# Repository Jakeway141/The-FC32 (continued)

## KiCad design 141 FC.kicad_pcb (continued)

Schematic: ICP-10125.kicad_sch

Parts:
C41, C43, C44, C75: 100nF; C_0603_1608Metric
C55: 1uF; C_0603_1608Metric
FB4: 1K/0.1A; L_0603_1608Metric
IC2: ICP-10125; ICP10125; Manufacturer_Part_Number ICP-10125; Mouser Part Number 410-ICP-10125
R17, R18: 3.3K; R_0603_1608Metric
R19, R20: 10K; R_0603_1608Metric
U2: SHT4x; Sensirion_DFN-4_1.5x1.5mm_P0.8mm_SHT4x_NoCentralPad
U6: TCA9517ADGK; VSSOP-8_3x3mm_P0.65mm

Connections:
/Barometer/SCL: R20.2, U2.2 (SCL), U6.7 (SCLB); also elsewhere on the board
/Barometer/SDA: R19.2, U2.1 (SDA), U6.6 (SDAB); also elsewhere on the board
/Barometer/SDA_BAR: IC2.4 (SDA), R18.2, U6.3 (SDAA)
unnamed: IC2.2 (SCL), R17.2, U6.2 (SCLA)
VDD: C44.1, R19.1, R20.1, U6.8 (VCCB); also elsewhere on the board
VDDBAR: C41.2, C43.2, C55.2, FB4.1, IC2.5 (VDD), R17.1, R18.1, U6.1 (VCCA)
VDDIMU_1_IO: C75.2, U2.3 (VDD); also elsewhere on the board
VDD_1V8: FB4.2; also elsewhere on the board

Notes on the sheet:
Level Shifting
Temperature Sensor

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
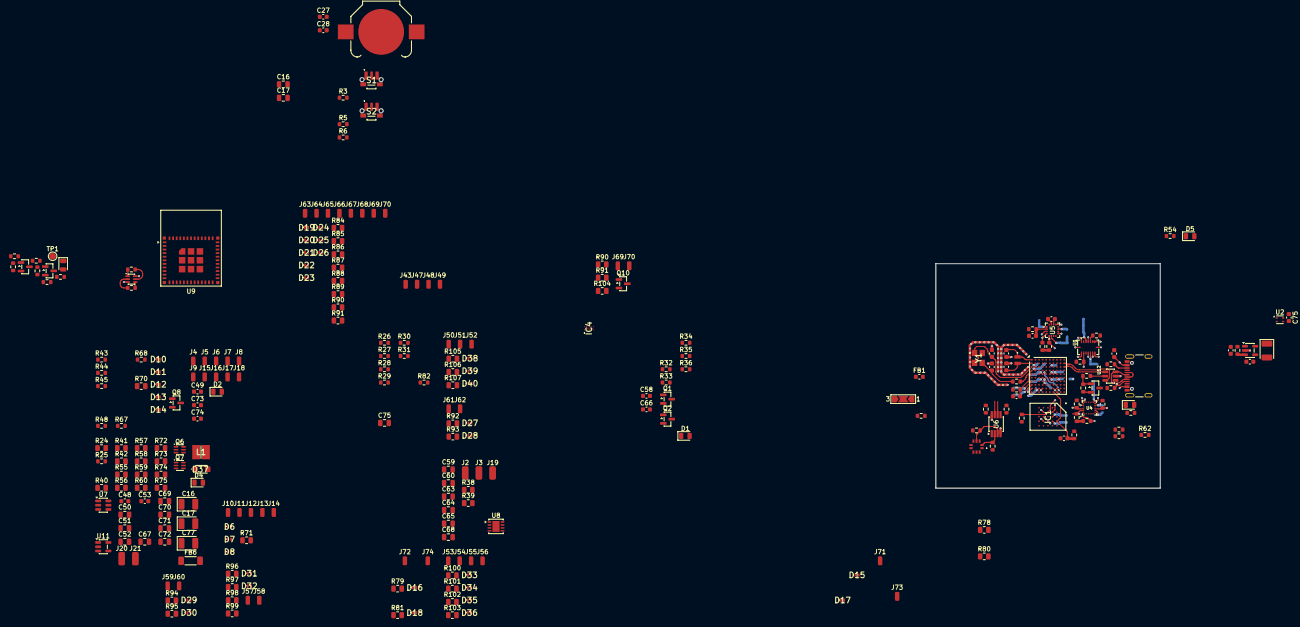
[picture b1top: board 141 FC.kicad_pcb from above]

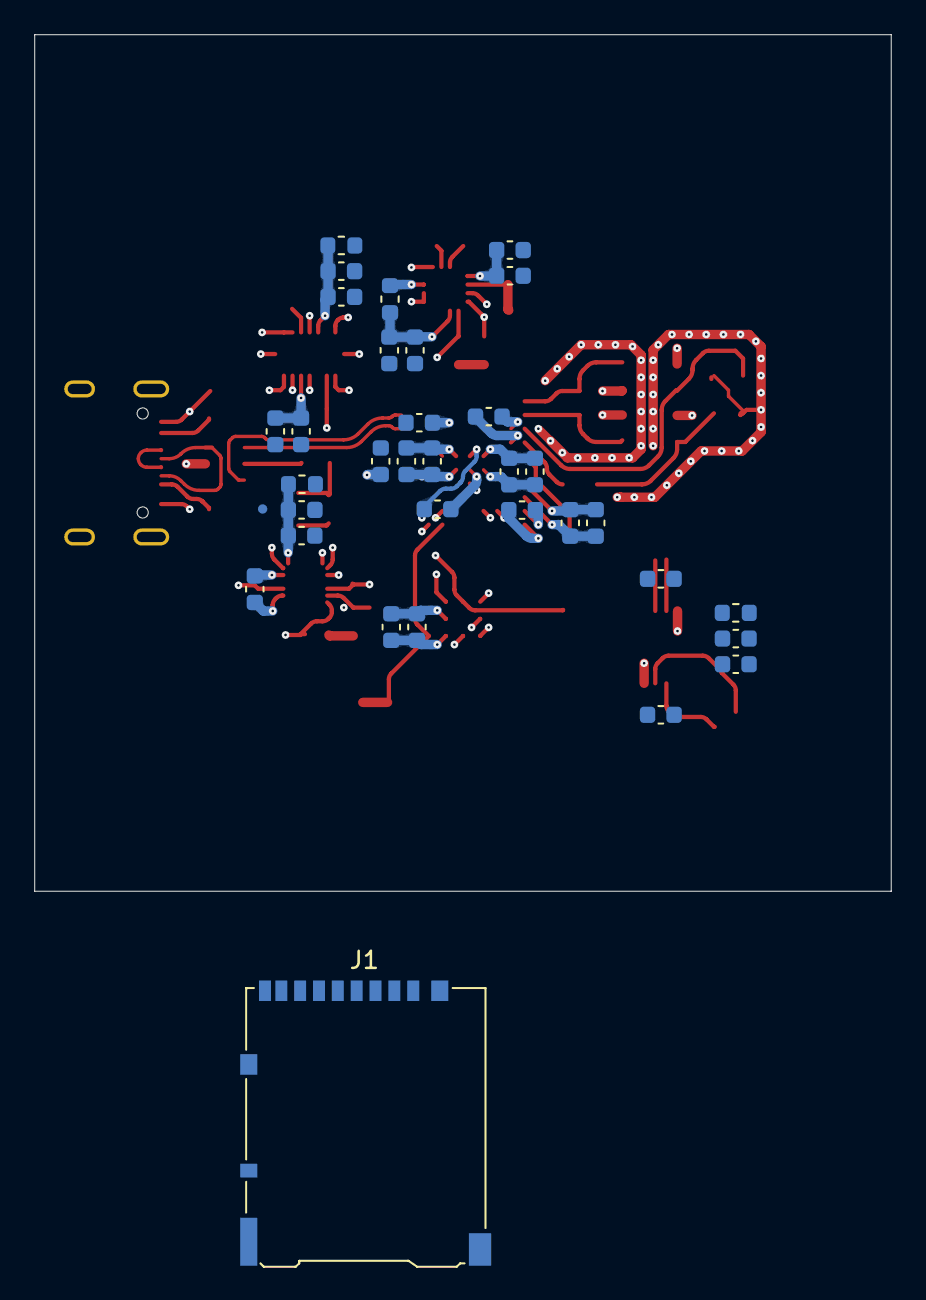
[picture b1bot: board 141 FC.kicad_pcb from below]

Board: 6 copper layers, 50.0 x 50.0 mm, 309 parts (33 on the bottom side), 190 nets.

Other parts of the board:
C16#2, C17#2, C75#2: 100nF; C_0805_2012Metric
D19, D20: PESD3V3X1BL,315; PESD5V0S1BL315
J43: M; SolderWirePad_1x01_SMD_1x2mm
J69#2: BZ+; SolderWirePad_1x01_SMD_1x2mm
J70#2: BZ-; SolderWirePad_1x01_SMD_1x2mm
R3: 220R; R_0603_1608Metric
R90#2: 22R; R_0805_2012Metric
R91#2: 10K; R_0805_2012Metric

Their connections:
/SD_Card/uSD_DET: C75#2.2; also elsewhere on the board

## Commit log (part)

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2026-04-10 Added Manually
2026-04-14 learning
2026-04-14 asdad
2026-04-20 Commit_1
2026-05-08 progress
2026-05-16 Almost Complete Schematic
2026-05-19 Stuck at BGA Fanout
2026-05-25 Package Change
2026-05-26 26/05/26
2026-05-26 abcd
2026-06-12 Layout Update 12th June
2026-06-20 Update 20/06/26
